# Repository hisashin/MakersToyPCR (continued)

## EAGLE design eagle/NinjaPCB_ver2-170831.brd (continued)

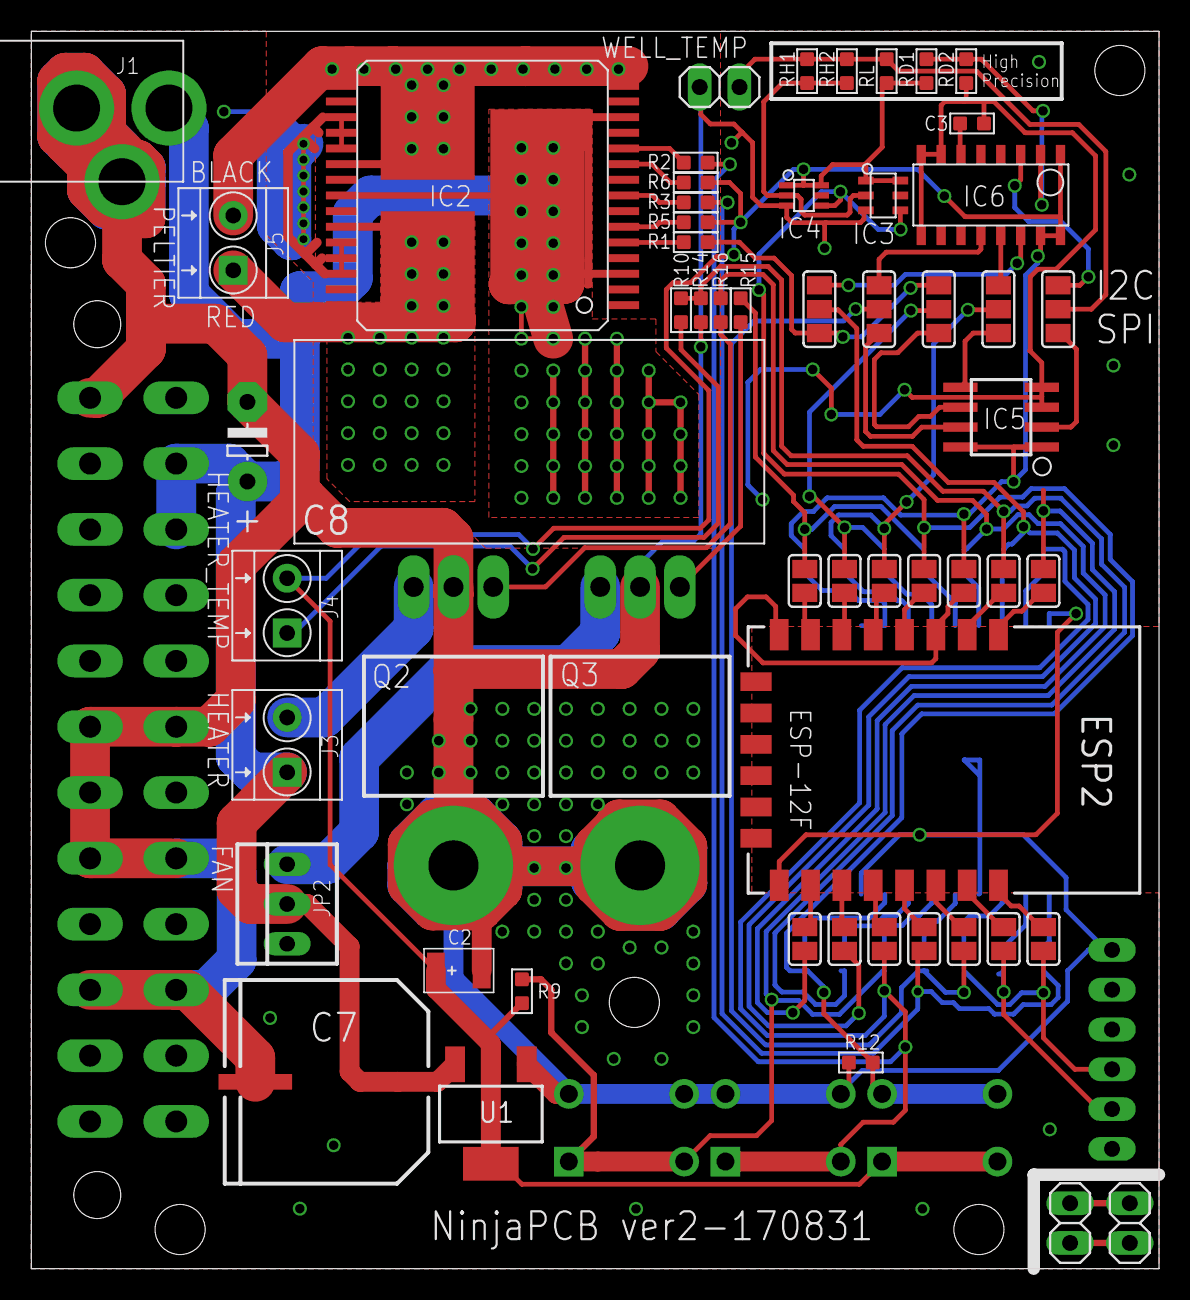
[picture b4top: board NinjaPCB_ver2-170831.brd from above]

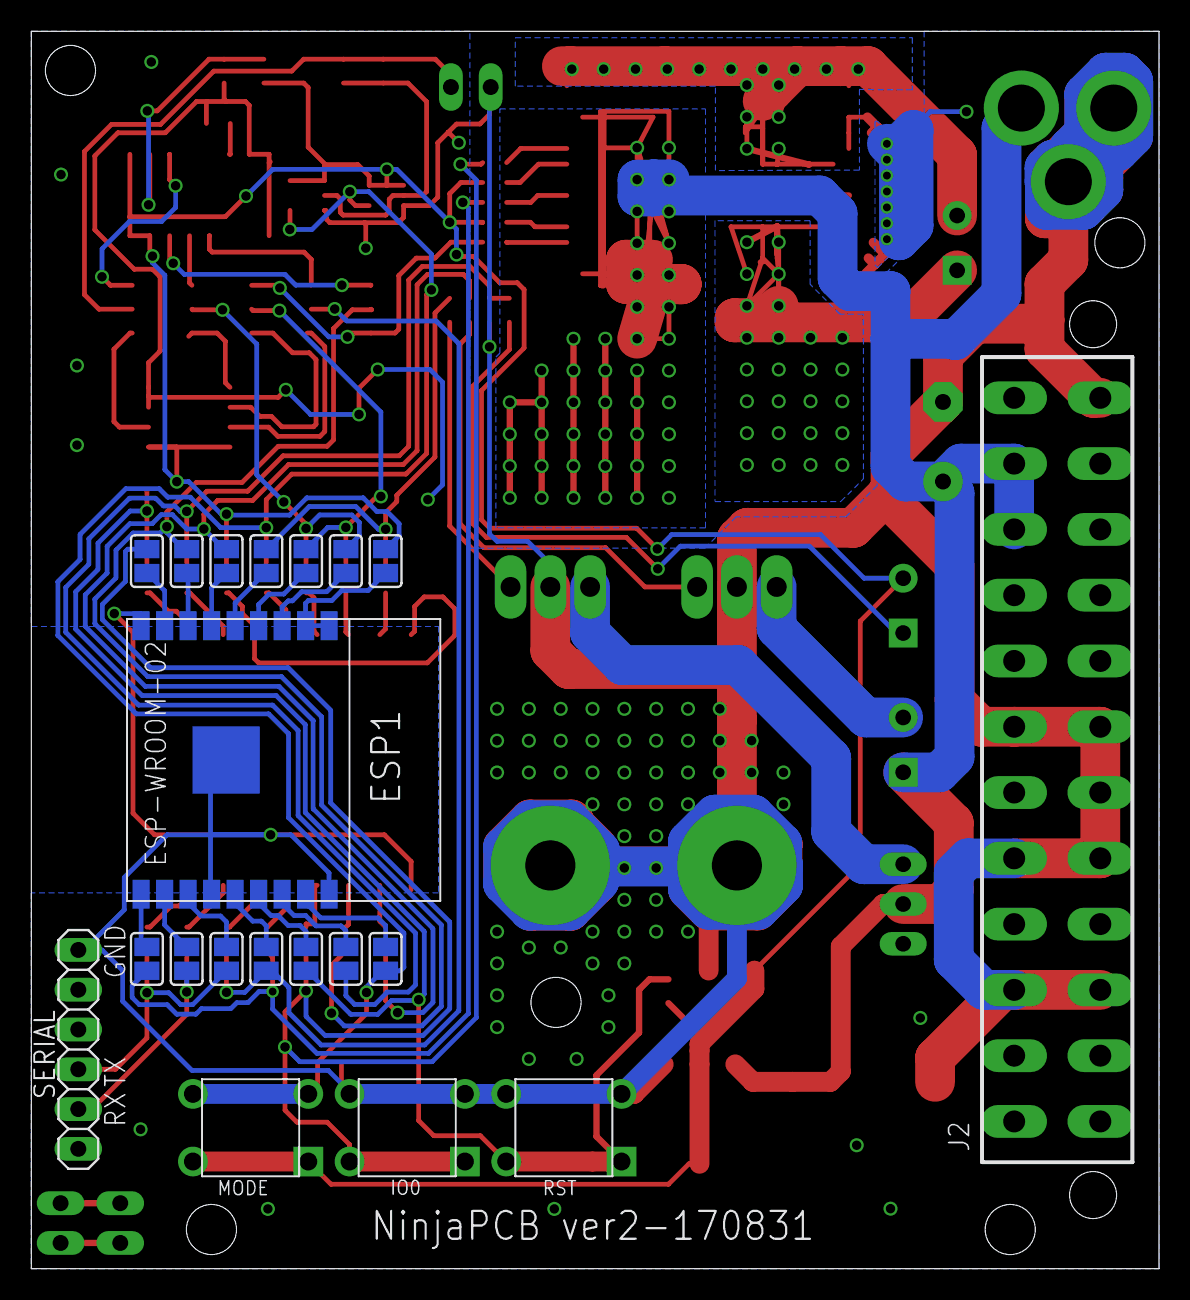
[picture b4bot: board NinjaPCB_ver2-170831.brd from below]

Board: 2 copper layers, 72.0 x 79.0 mm, 76 parts (20 on the bottom side), 71 nets.

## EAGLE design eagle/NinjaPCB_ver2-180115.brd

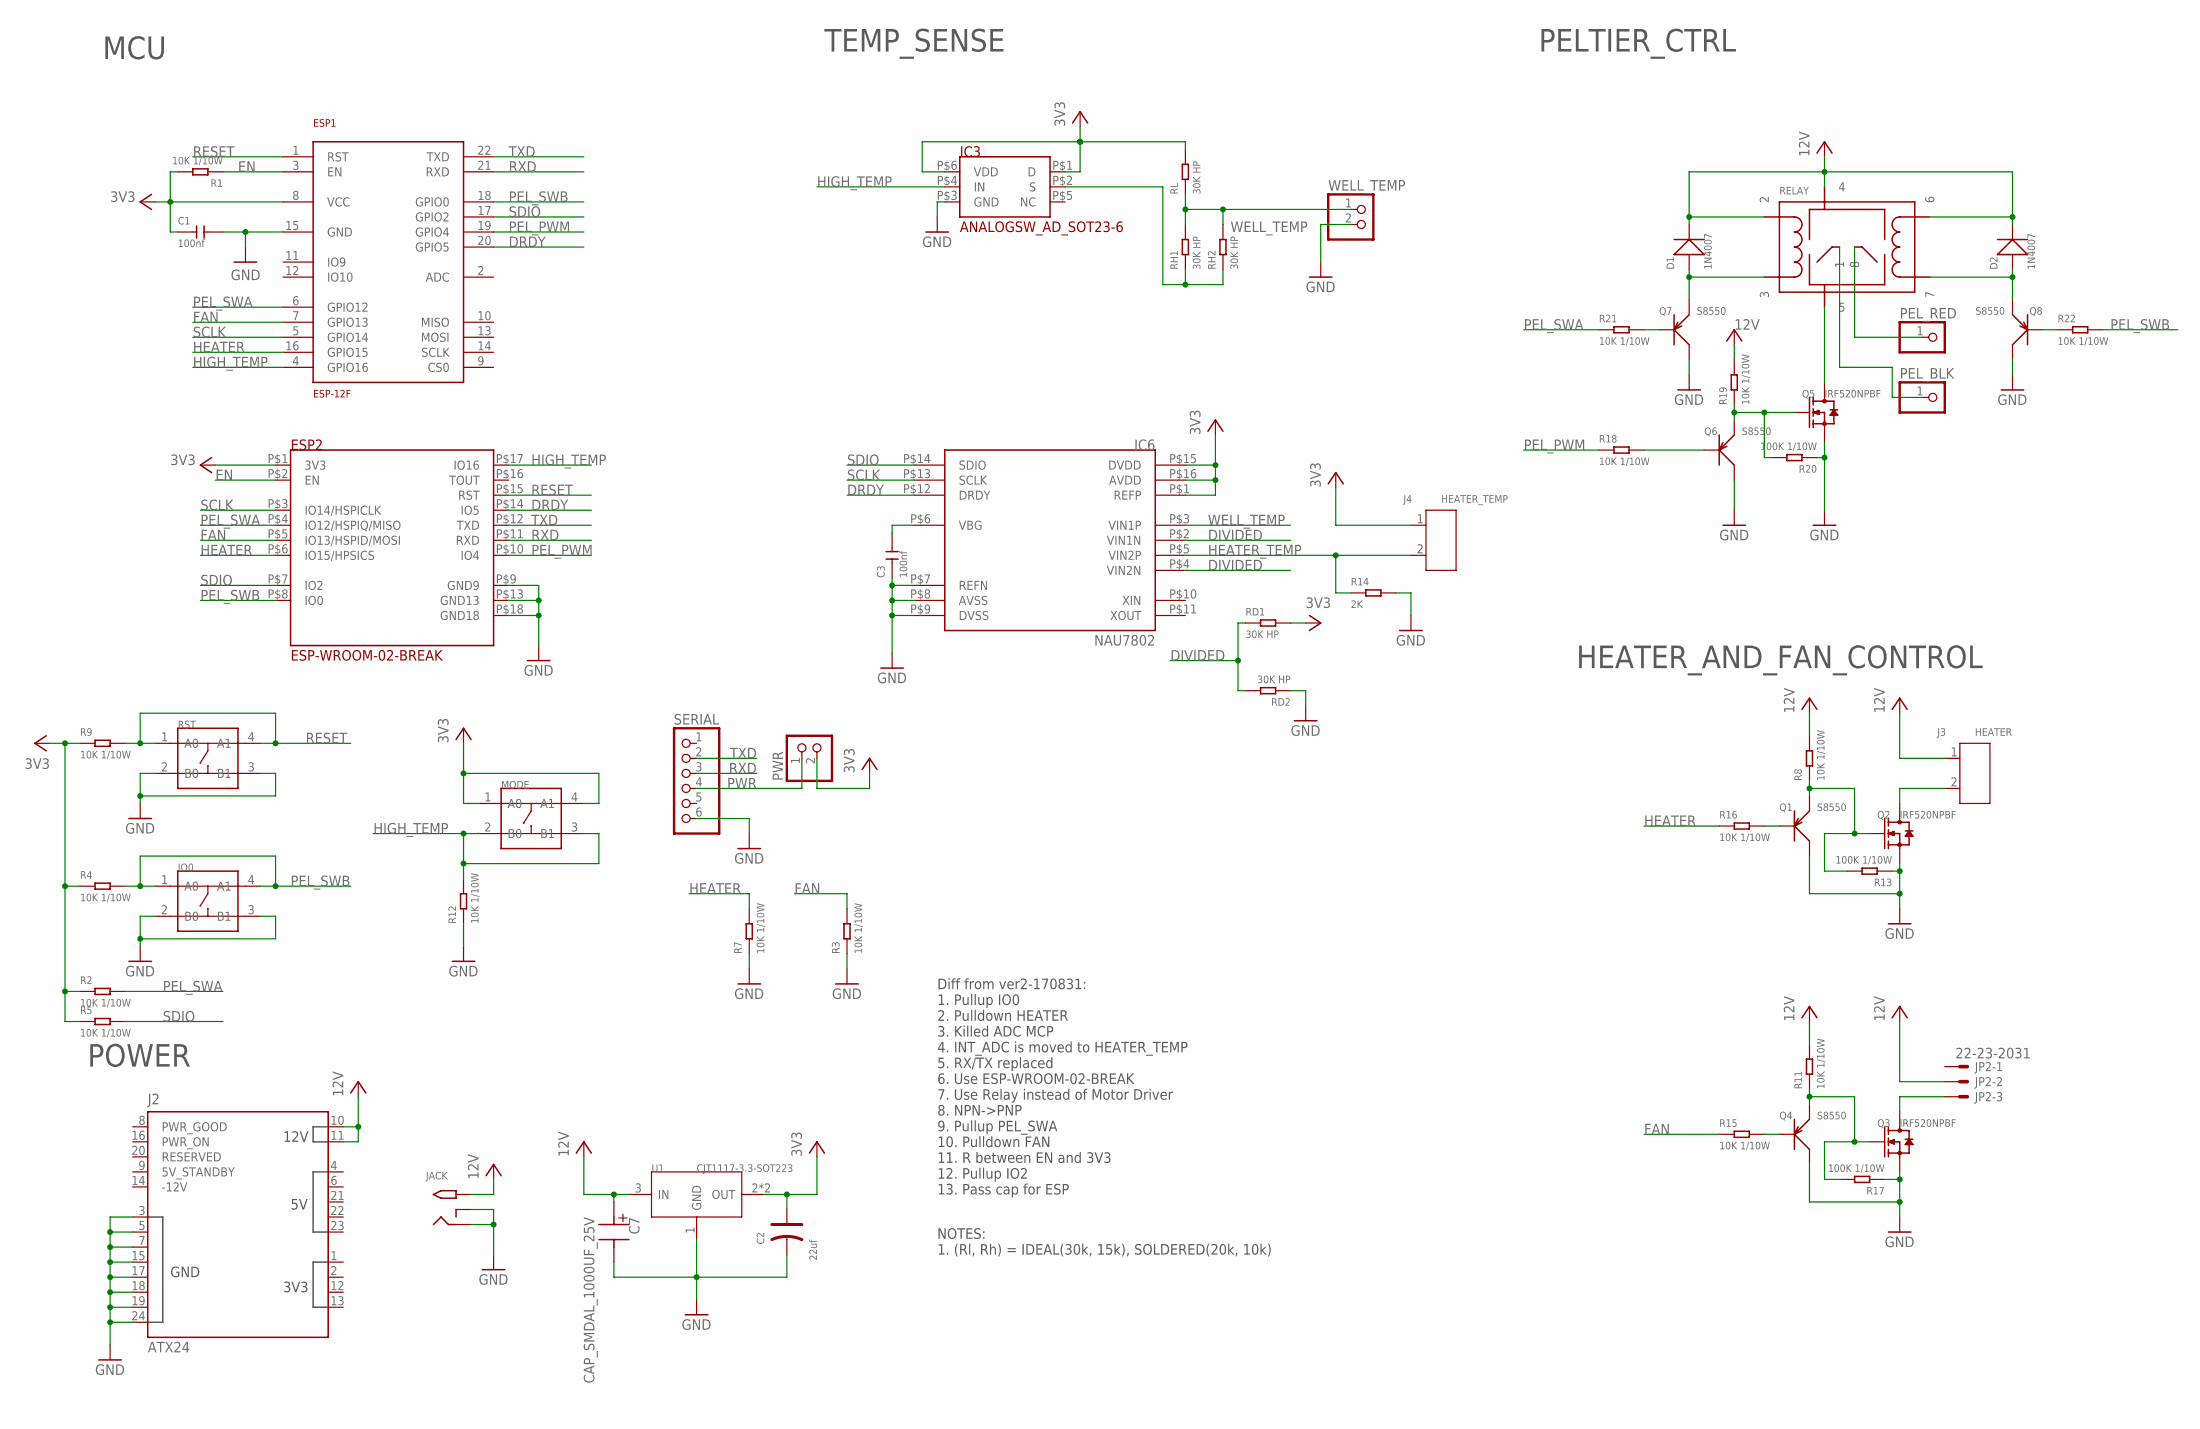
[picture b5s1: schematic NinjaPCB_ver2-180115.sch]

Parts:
C1, C3: 100nf; C0603
C2: 22uf; AVX-B
C7: CAP_SMDAL_1000UF_25V; CAP_SMD_AL_D125
D1, D2: 1N4007; DO-214AC
ESP1: ESP-12F
ESP2: ESP-WROOM-02-BREAK
IC3: ANALOGSW_AD_SOT23-6; SOT-23-6
IC6: NAU7802; SOP-16
IO0: DIP-SWITCH-TACTILE-SPST-NO/TS-1109(4P-D6.0MM)'TS-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; SW4-6.0X6.0X5.0MM
J2: ATX24
J3: HEATER; H2-3.5-7.0X7.0MM
J4: HEATER_TEMP; H2-3.5-7.0X7.0MM
JACK: 2.1MMJACKTHM; PJ-102A
JP2: 22-23-2031
MODE: DIP-SWITCH-TACTILE-SPST-NO/TS-1109(4P-D6.0MM)'TS-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; SW4-6.0X6.0X5.0MM
PEL_BLK: PINHD-1X1L; 1X01LONG
PEL_RED: PINHD-1X1L; 1X01LONG
PWR: PINHD-1X2; 1X02
Q1, Q4, Q6, Q7, Q8: S8550; SOT-23
Q2, Q3, Q5: IRF520NPBF; TO-220
R1, R2, R3, R4, R5, R7, R8, R9, R11, R12, R15, R16, R18, R19, R21, R22: 10K 1/10W; R0603
R13, R17, R20: 100K 1/10W; R0603
R14: 2K; R0603
RD1, RD2: 30K HP; R0603
RELAY: NEC-RELAY2ET2; NEC-ET2-N8
RH1, RH2: 30K HP; R0603
RL: 30K HP; R0603
RST: DIP-SWITCH-TACTILE-SPST-NO/TS-1109(4P-D6.0MM)'TS-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; SW4-6.0X6.0X5.0MM
SERIAL: PINHD-1X6; 1X06
U1: CJT1117-3.3-SOT223; SOT-223
WELL_TEMP: PINHD-1X2; 1X02

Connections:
3V3: C1.1, C2.+, ESP1.8 (VCC), ESP2.P$1 (3V3), IC3.P$1 (D), IC3.P$6 (VDD), IC6.P$1 (REFP), IC6.P$15 (DVDD), IC6.P$16 (AVDD), J4.1, MODE.1 (A0), MODE.4 (A1), PWR.2, R1.2, R2.1, R4.1, R5.1, R9.1, RD1.2, RL.2, U1.2 (OUT), U1.TER (OUT)
12V: C7.P$P, D1.2 (-), D2.2 (-), J2.10 (12V_10), J2.11 (12V_11), J3.1, JACK.TIP, JP2.2, R8.2, R11.2, R19.2, RELAY.P$2 (2), RELAY.P$4 (4), RELAY.P$6 (6), U1.3 (IN)
DIVIDED: IC6.P$2 (VIN1N), IC6.P$4 (VIN2N), RD1.1, RD2.2
DRDY: ESP1.20 (GPIO5), ESP2.P$14 (IO5), IC6.P$12 (DRDY)
EN: ESP1.3 (EN), ESP2.P$2 (EN), R1.1
FAN: ESP1.7 (GPIO13), ESP2.P$5 (IO13/HSPID/MOSI), R3.2, R15.1
GND: C1.2, C2.-, C3.1, C7.P$M, ESP1.15 (GND), ESP2.P$9 (GND9), ESP2.P$13 (GND13), ESP2.P$18 (GND18), IC3.P$3 (GND), IC6.P$7 (REFN), IC6.P$8 (AVSS), IC6.P$9 (DVSS), IO0.2 (B0), IO0.3 (B1), J2.3 (GND3), J2.5 (GND5), J2.7 (GND7), J2.15 (GND15), J2.17 (GND17), J2.18 (GND18), J2.19 (GND19), J2.24 (GND24), JACK.RING, JACK.RING_SW, Q1.3 (C), Q2.3 (S), Q3.3 (S), Q4.3 (C), Q5.3 (S), Q6.3 (C), Q7.3 (C), Q8.3 (C), R3.1, R7.1, R12.1, R13.1, R14.2, R17.1, R20.1, RD2.1, RST.2 (B0), RST.3 (B1), SERIAL.6, U1.1 (GND), WELL_TEMP.2
HEATER: ESP1.16 (GPIO15), ESP2.P$6 (IO15/HPSICS), R7.2, R16.1
HEATER_TEMP: IC6.P$5 (VIN2P), J4.2, R14.1
HIGH_TEMP: ESP1.4 (GPIO16), ESP2.P$17 (IO16), IC3.P$4 (IN), MODE.2 (B0), MODE.3 (B1), R12.2
unnamed: J3.2, Q2.2 (D), Q2.HEAT (D)
unnamed: Q5.2 (D), Q5.HEAT (D), RELAY.P$5 (5)
unnamed: JP2.3, Q3.2 (D), Q3.HEAT (D)
unnamed: Q5.1 (G), Q6.2 (E), R19.1, R20.2
unnamed: PEL_RED.1, RELAY.P$8 (8)
unnamed: PEL_BLK.1, RELAY.P$1 (1)
unnamed: Q3.1 (G), Q4.2 (E), R11.1, R17.2
unnamed: IC3.P$2 (S), RH1.1, RH2.1
unnamed: Q1.2 (E), Q2.1 (G), R8.1, R13.2
unnamed: Q6.1 (B), R18.2
unnamed: Q4.1 (B), R15.2
unnamed: Q1.1 (B), R16.2
unnamed: D1.1 (+), Q7.2 (E), RELAY.P$3 (3)
unnamed: Q7.1 (B), R21.2
unnamed: Q8.1 (B), R22.1
unnamed: D2.1 (+), Q8.2 (E), RELAY.P$7 (7)
unnamed: C3.2, IC6.P$6 (VBG)
PEL_PWM: ESP1.19 (GPIO4), ESP2.P$10 (IO4), R18.1
PEL_SWA: ESP1.6 (GPIO12), ESP2.P$4 (IO12/HSPIQ/MISO), R2.2, R21.1
PEL_SWB: ESP1.18 (GPIO0), ESP2.P$8 (IO0), IO0.1 (A0), IO0.4 (A1), R4.2, R22.2
PWR: PWR.1, SERIAL.4
RESET: ESP1.1 (RST), ESP2.P$15 (RST), R9.2, RST.1 (A0), RST.4 (A1)
RXD: ESP1.21 (RXD), ESP2.P$11 (RXD), SERIAL.3
SCLK: ESP1.5 (GPIO14), ESP2.P$3 (IO14/HSPICLK), IC6.P$13 (SCLK)
SDIO: ESP1.17 (GPIO2), ESP2.P$7 (IO2), IC6.P$14 (SDIO), R5.2
TXD: ESP1.22 (TXD), ESP2.P$12 (TXD), SERIAL.2
WELL_TEMP: IC6.P$3 (VIN1P), RH1.2, RH2.2, RL.1, WELL_TEMP.1

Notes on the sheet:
TEMP_SENSE
HEATER_AND_FAN_CONTROL
PELTIER_CTRL
MCU
POWER
NOTES: 1. (Rl, Rh) = IDEAL(30k, 15k), SOLDERED(20k, 10k)
Diff from ver2-170831: 1. Pullup IO0 2. Pulldown HEATER 3. Killed ADC MCP 4. INT_ADC is moved to HEATER_TEMP 5. RX/TX replaced 6. Use ESP-WROOM-02-BREAK 7. Use Relay instead of Motor Driver 8. NPN->PNP 9. Pullup PEL_SWA 10. Pulldown FAN 11. R between EN and 3V3 12. Pullup IO2 13. Pass cap for ESP

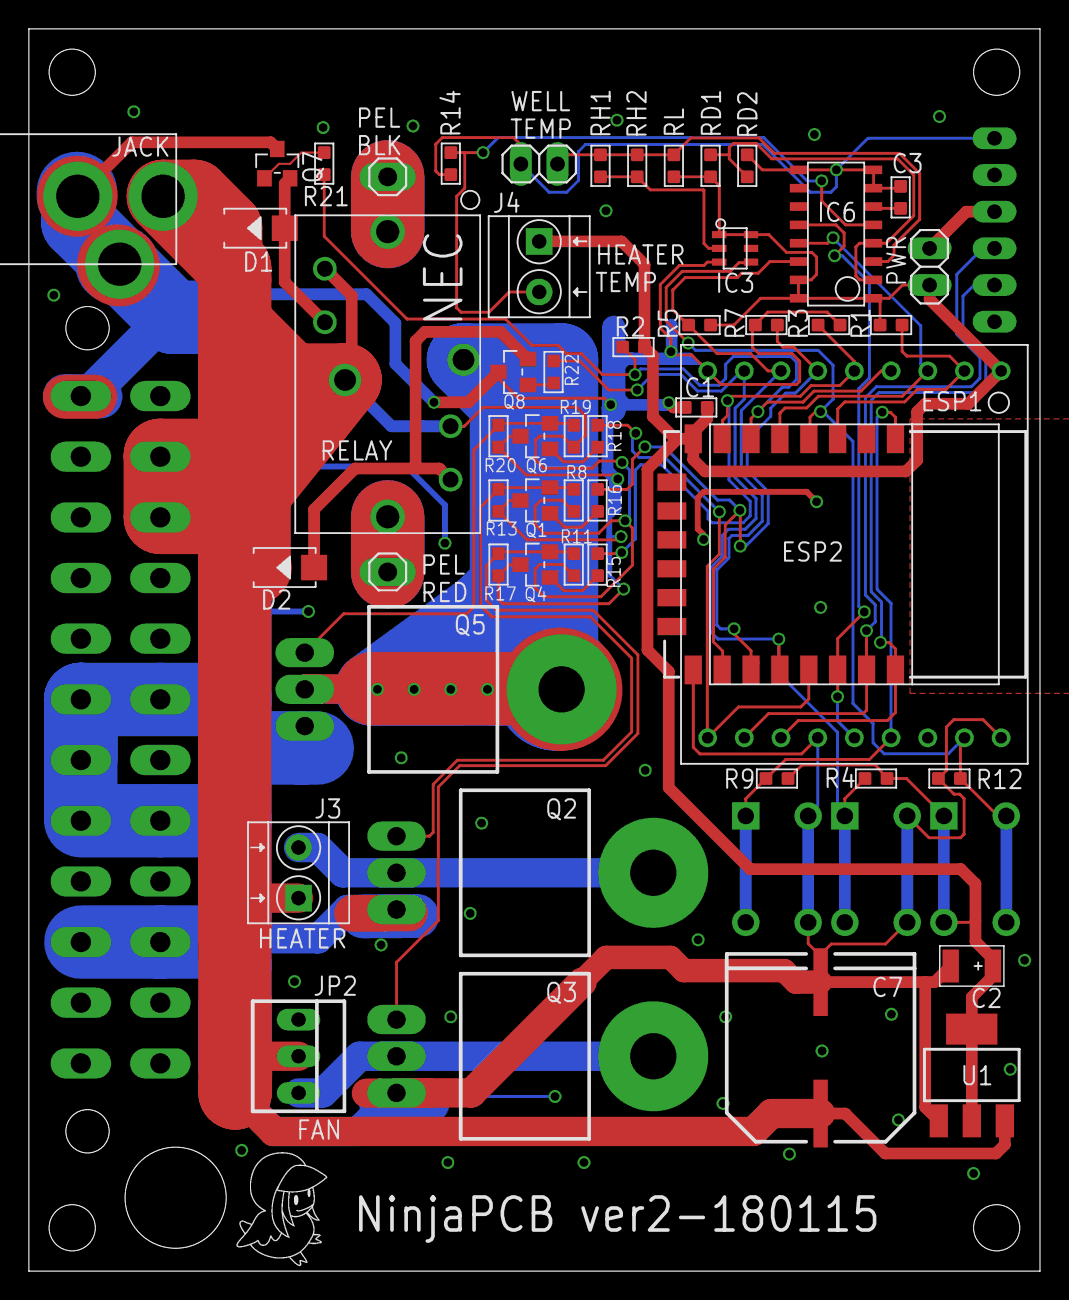
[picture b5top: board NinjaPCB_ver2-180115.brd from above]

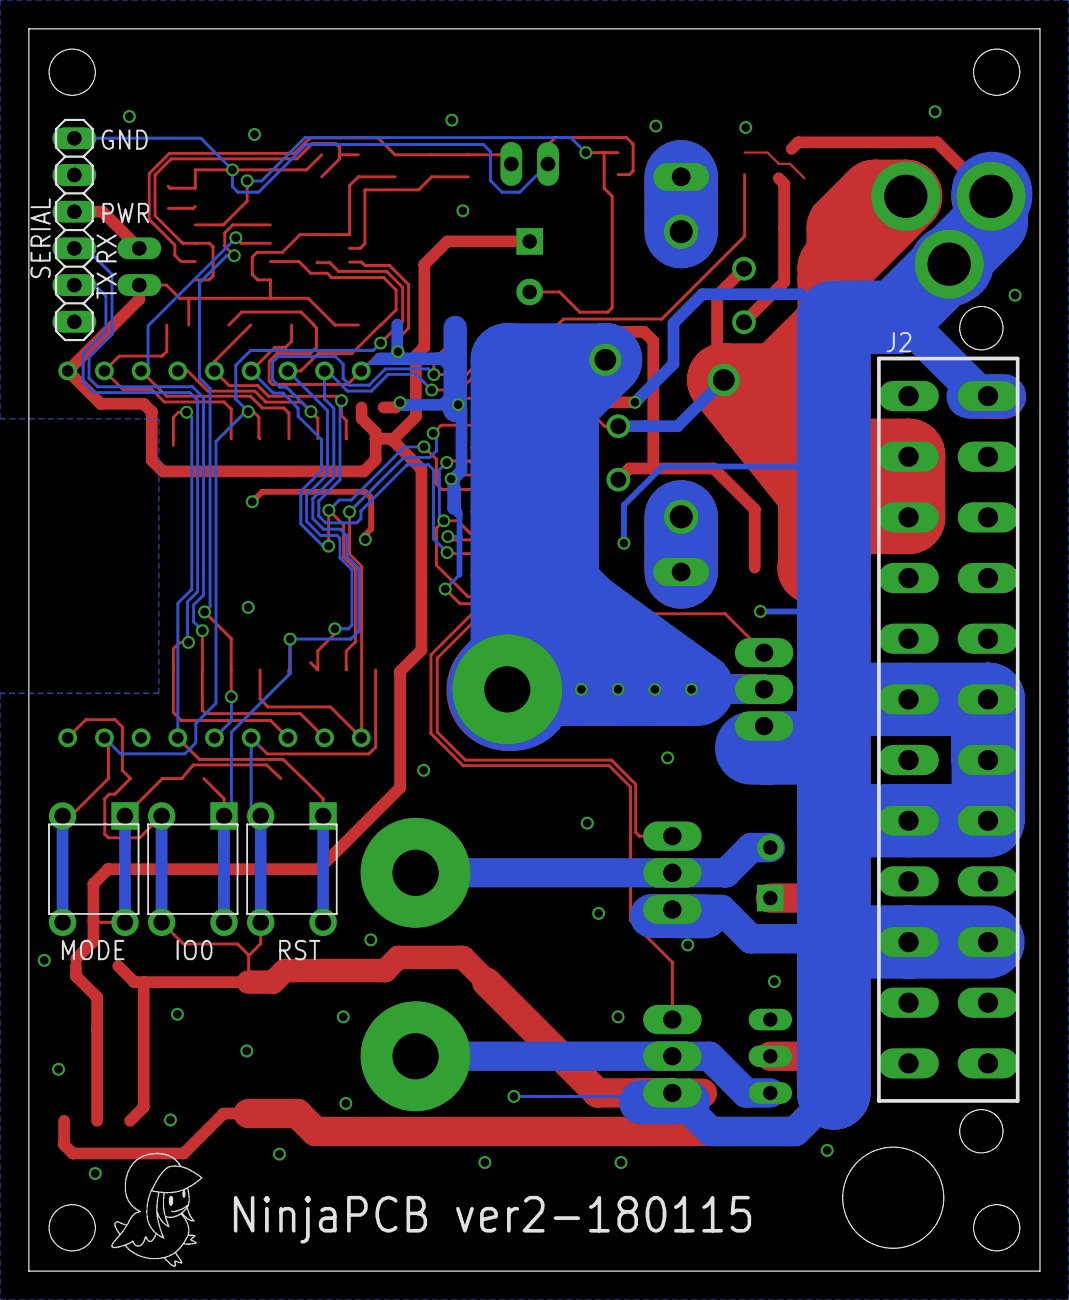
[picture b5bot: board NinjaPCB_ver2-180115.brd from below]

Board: 2 copper layers, 70.0 x 86.0 mm, 60 parts (6 on the bottom side), 37 nets.

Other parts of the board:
U$1, U$2: TORI_0.25

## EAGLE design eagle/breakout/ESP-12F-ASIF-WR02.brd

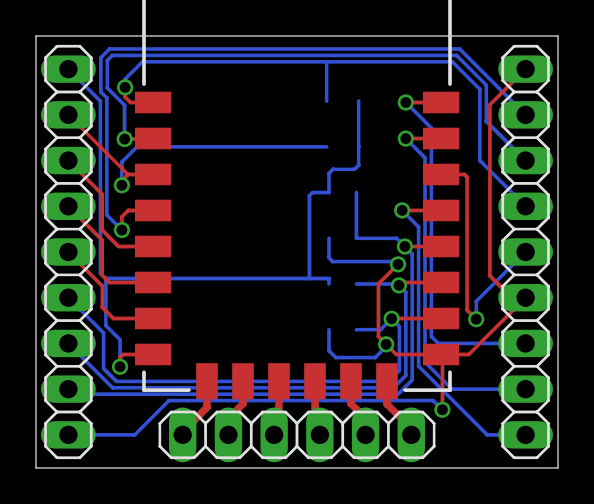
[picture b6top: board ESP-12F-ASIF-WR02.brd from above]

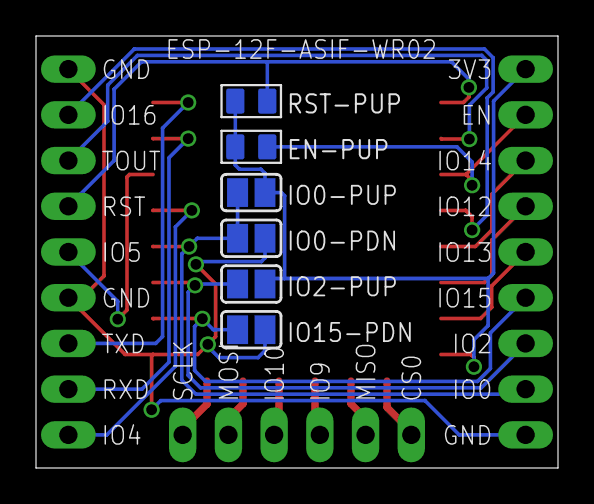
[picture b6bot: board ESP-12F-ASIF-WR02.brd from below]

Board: 2 copper layers, 29.0 x 24.0 mm, 10 parts (6 on the bottom side), 22 nets.

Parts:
EN-PUP: 10K; R0805
IO0-PDN, IO0-PUP, IO2-PUP, IO15-PDN: SJ
JP1: 1X06
LEFT: 1X09
RIGHT: 1X09
RST-PUP: 10K; R0805
U1: ESP-12F

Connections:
3V3: EN-PUP.2, IO0-PUP.1, IO2-PUP.1, LEFT.1, RST-PUP.2, U1.8
CS0: JP1.1, U1.9
EN: EN-PUP.1, LEFT.2, U1.3
GND: IO0-PDN.1, IO15-PDN.1, LEFT.9, RIGHT.1, RIGHT.6, U1.15
IO0: IO0-PDN.2, IO0-PUP.2, LEFT.8, U1.18
IO2: IO2-PUP.2, LEFT.7, U1.17
IO4: RIGHT.9, U1.19
IO5: RIGHT.5, U1.20
IO9: JP1.3, U1.11
IO10: JP1.4, U1.12
IO12: LEFT.4, U1.6
IO13: LEFT.5, U1.7
IO14: LEFT.3, U1.5
IO15: IO15-PDN.2, LEFT.6, U1.16
IO16: RIGHT.2, U1.4
MISO: JP1.2, U1.10
MOSI: JP1.5, U1.13
RST: RIGHT.4, RST-PUP.1, U1.1
RXD: RIGHT.8, U1.21
SCLK: JP1.6, U1.14
TOUT: RIGHT.3, U1.2
TXD: RIGHT.7, U1.22
